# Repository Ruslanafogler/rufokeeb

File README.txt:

A personal keyboard I am developing from scratch using kicad for fun! Attached are the pcb files and gerbers invovled, BOM is also included. 67% keeb, based off of the KBD67 Lite.

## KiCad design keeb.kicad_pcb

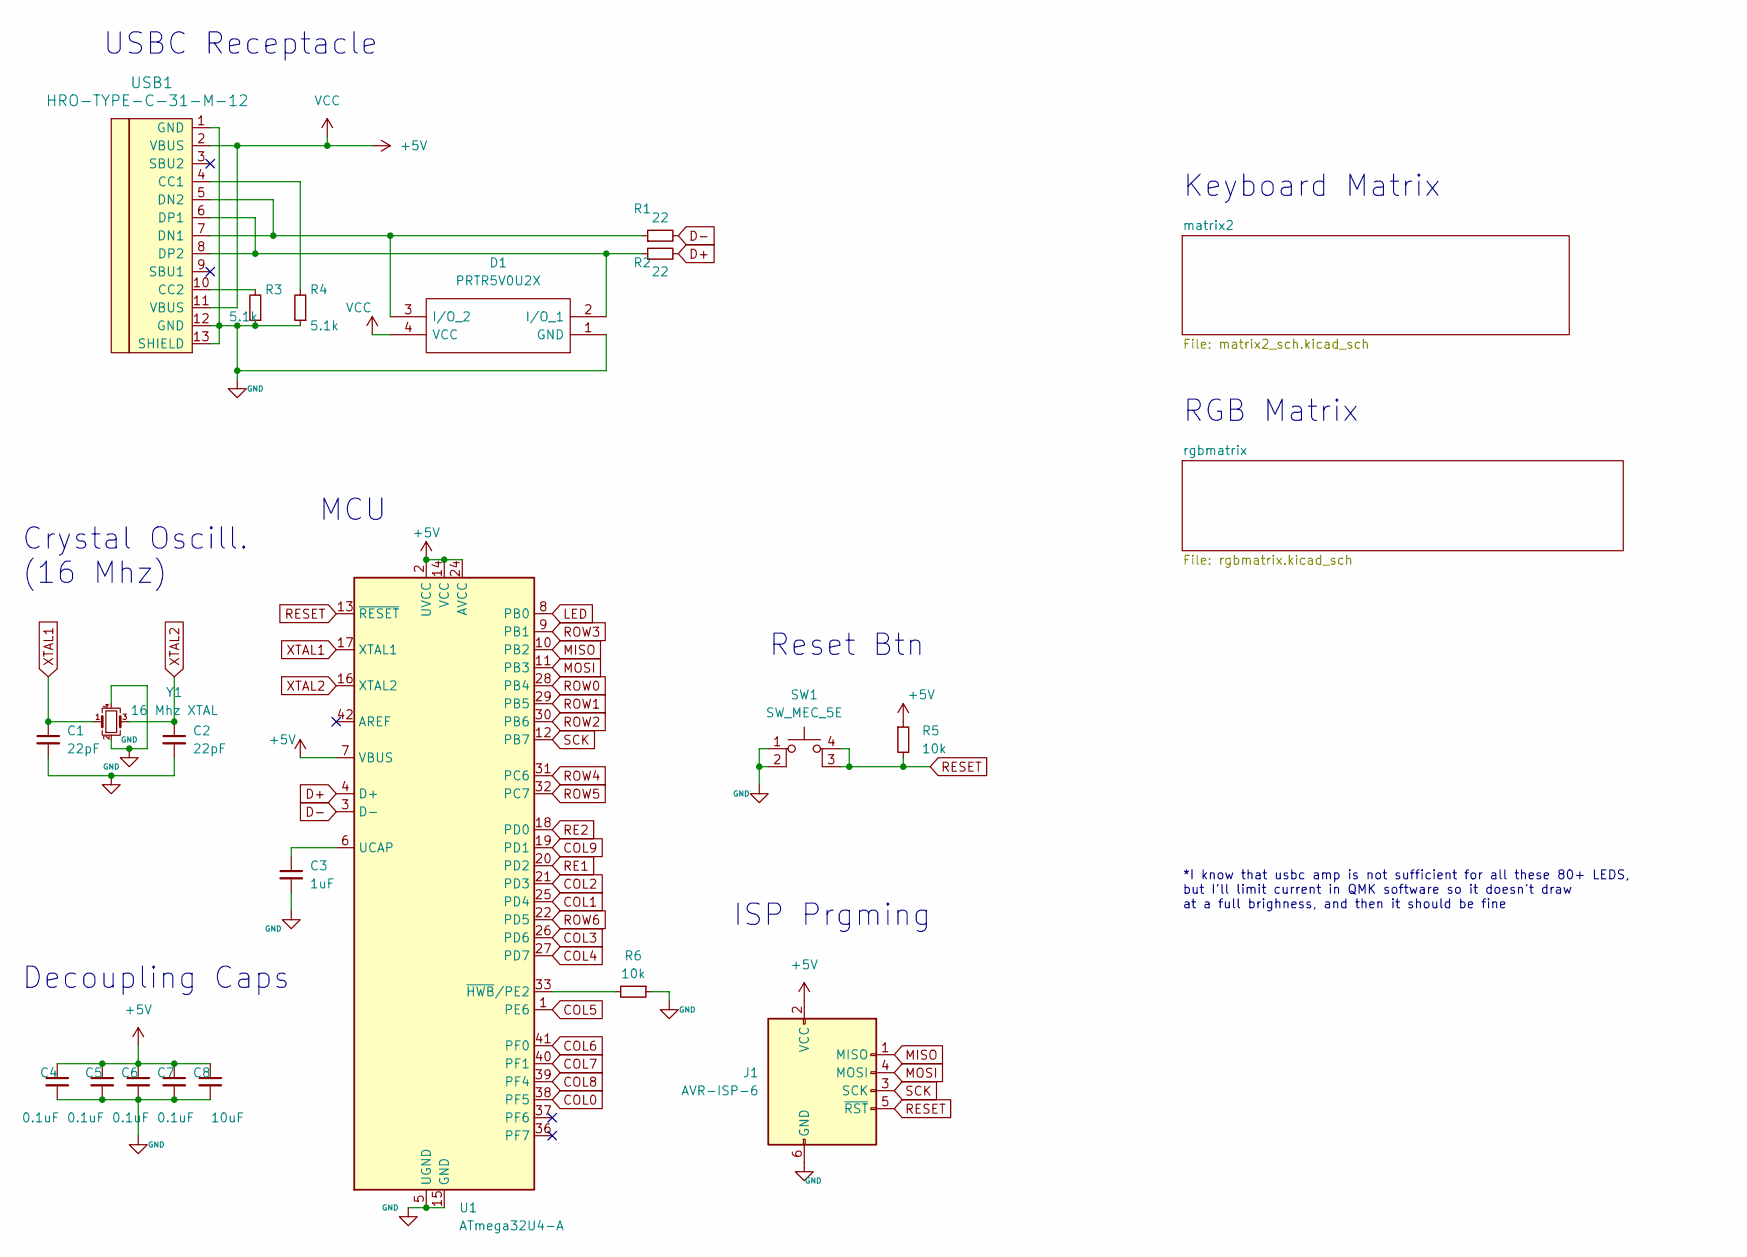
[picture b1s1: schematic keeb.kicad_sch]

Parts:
C1, C2: 22pF; C_0805_2012Metric_Pad1.18x1.45mm_HandSolder
C3: 1uF; C_0805_2012Metric_Pad1.18x1.45mm_HandSolder
C4, C5, C6, C7: 0.1uF; C_0805_2012Metric_Pad1.18x1.45mm_HandSolder
C8: 10uF; C_0805_2012Metric_Pad1.18x1.45mm_HandSolder
D1: PRTR5V0U2X; SOT143B; Manufacturer_Part_Number PRTR5V0U2X; Mouser Part Number N/A
J1: AVR-ISP-6; Reset_Pretty-Mask
R1, R2: 22; R_0805_2012Metric_Pad1.20x1.40mm_HandSolder
R3, R4: 5.1k; R_0805_2012Metric_Pad1.20x1.40mm_HandSolder
R5, R6: 10k; R_0805_2012Metric_Pad1.20x1.40mm_HandSolder
SW1: SW_MEC_5E; SW_MEC_5GSH9
U1: ATmega32U4-A; TQFP-44_10x10mm_P0.8mm
USB1: HRO-TYPE-C-31-M-12; HRO-TYPE-C-31-M-12-HandSoldering
Y1: 16 Mhz XTAL; Crystal_SMD_3225-4Pin_3.2x2.5mm_HandSoldering

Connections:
+5V: C4.1, C5.1, C6.1, C7.1, C8.1, D1.4 (VCC), J1.2 (VCC), R5.1, U1.2 (UVCC), U1.7 (VBUS), U1.14 (VCC), U1.24 (AVCC), U1.34 (VCC), U1.44 (AVCC), USB1.2 (VBUS), USB1.11 (VBUS); also elsewhere on the board
COL0: U1.38 (PF5); also elsewhere on the board
COL1: U1.25 (PD4); also elsewhere on the board
COL2: U1.21 (PD3); also elsewhere on the board
COL3: U1.26 (PD6); also elsewhere on the board
COL4: U1.27 (PD7); also elsewhere on the board
COL5: U1.1 (PE6); also elsewhere on the board
COL6: U1.41 (PF0); also elsewhere on the board
COL7: U1.40 (PF1); also elsewhere on the board
COL8: U1.39 (PF4); also elsewhere on the board
COL9: U1.19 (PD1); also elsewhere on the board
D+: R2.2, U1.4 (D+)
D-: R1.2, U1.3 (D-)
GND: C1.2, C2.2, C3.2, C4.2, C5.2, C6.2, C7.2, C8.2, D1.1 (GND), J1.6 (GND), R3.1, R4.1, R6.1, SW1.1, SW1.2, U1.5 (UGND), U1.15 (GND), U1.23 (GND), U1.35 (GND), U1.43 (GND), USB1.1 (GND), USB1.12 (GND), USB1.13 (SHIELD), Y1.2, Y1.4; also elsewhere on the board
LED: U1.8 (PB0); also elsewhere on the board
unnamed: C3.1, U1.6 (UCAP)
unnamed: D1.2 (I/O_1), R2.1, USB1.6 (DP1), USB1.8 (DP2)
unnamed: D1.3 (I/O_2), R1.1, USB1.5 (DN2), USB1.7 (DN1)
unnamed: R3.2, USB1.10 (CC2)
unnamed: R4.2, USB1.4 (CC1)
unnamed: R6.2, U1.33 (~HWB/PE2)
RE1: U1.20 (PD2); also elsewhere on the board
RE2: U1.18 (PD0); also elsewhere on the board
RESET: J1.5 (~RST), R5.2, SW1.3 (K), SW1.4 (A), U1.13 (~RESET); also elsewhere on the board
ROW0: U1.28 (PB4); also elsewhere on the board
ROW1: U1.29 (PB5); also elsewhere on the board
ROW2: U1.30 (PB6); also elsewhere on the board
ROW4: U1.31 (PC6); also elsewhere on the board
ROW5: U1.32 (PC7); also elsewhere on the board
ROW6: U1.22 (PD5); also elsewhere on the board
XTAL1: C1.1, U1.17 (XTAL1), Y1.1
XTAL2: C2.1, U1.16 (XTAL2), Y1.3

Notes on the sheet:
MCU
ISP Prgming
RGB Matrix
Reset Btn
USBC Receptacle
Keyboard Matrix
Crystal Oscill. (16 Mhz)
Decoupling Caps
*I know that usbc amp is not sufficient for all these 80+ LEDS, but I'll limit current in QMK software so it doesn't draw at a full brighness, and then it should be fine

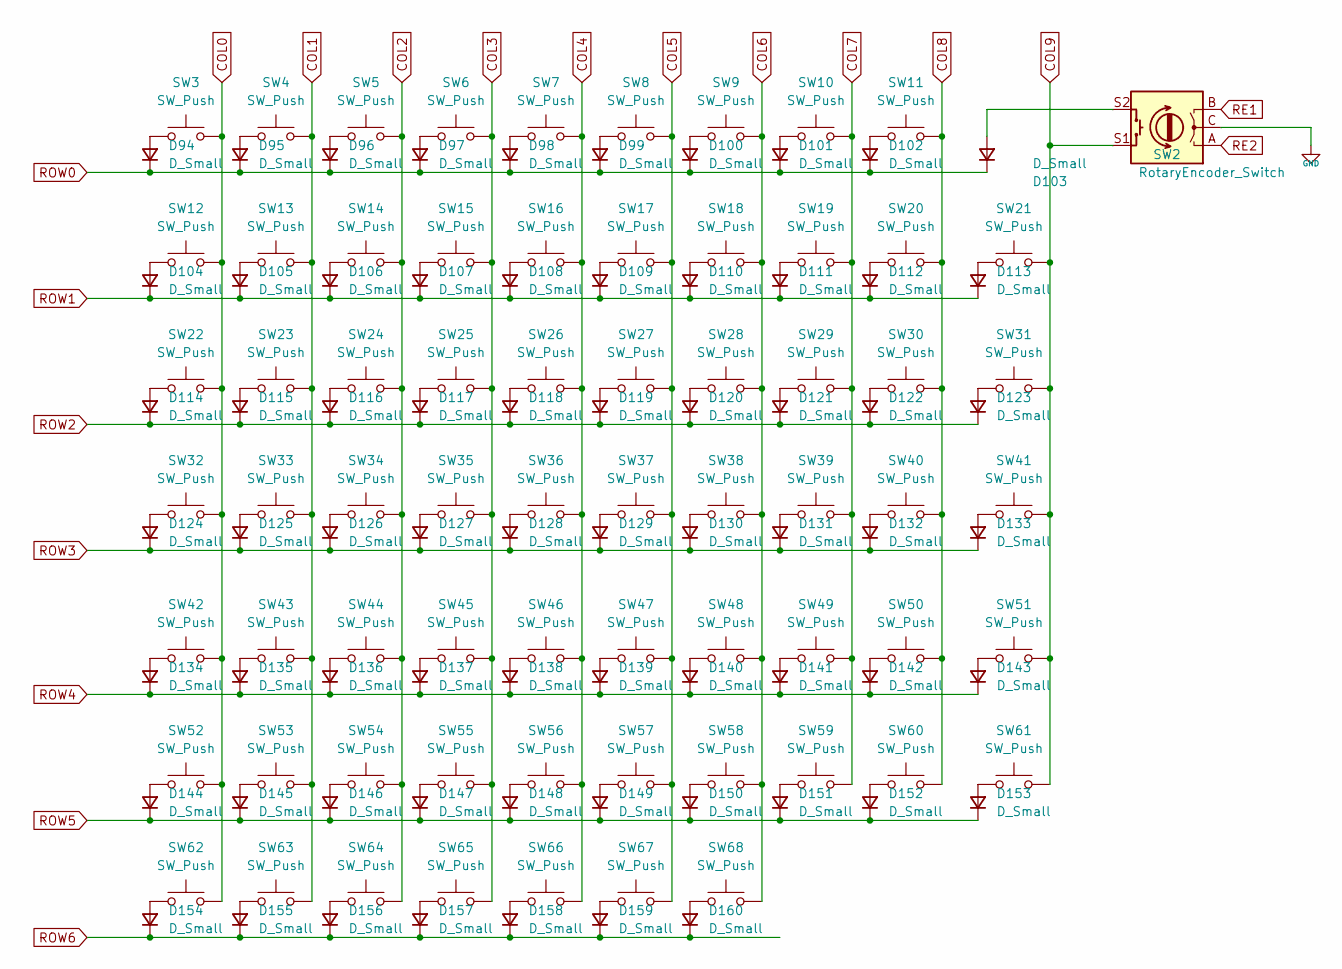
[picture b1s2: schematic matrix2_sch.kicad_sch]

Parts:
D94, D95, D96, D97, D98, D99, D100, D101, D102, D103, D104, D105, D106, D107, D108, D109, D110, D111, D112, D113, D114, D115, D116, D117, D118, D119, D120, D121, D122, D123, D124, D125, D126, D127, D128, D129, D130, D131, D132, D133, D134, D135, D136, D137, D138, D139, D140, D141, D142, D143, D144, D145, D146, D147, D148, D149, D150, D151, D152, D153, D154, D155, D156, D157, D158, D159, D160: D_Small; D_SOD-123
SW2: RotaryEncoder_Switch; RotaryEncoder_Alps_EC11E-Switch_Vertical_H20mm_CircularMoun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
SW3, SW4, SW5, SW6, SW7, SW8, SW9, SW10, SW11, SW12, SW13, SW14, SW15, SW18, SW19, SW20, SW21, SW22, SW23, SW24, SW25, SW26, SW27, SW28, SW29, SW31, SW33, SW34, SW35, SW36, SW37, SW38, SW39, SW40, SW41, SW42, SW43, SW45, SW47, SW48, SW49, SW50, SW51, SW52, SW53, SW54, SW55, SW56, SW58, SW59, SW66, SW67, SW68: SW_Push; MX100H
SW16: SW_Push; MX200HR
SW17, SW30: SW_Push; MX150H
SW32, SW57: SW_Push; MX175H
SW44, SW46: SW_Push; MX225HR
SW60, SW61, SW62, SW64, SW65: SW_Push; MX125H
SW63: SW_Push; MX625HR

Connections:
COL0: SW3.2, SW12.2, SW22.2, SW32.2, SW42.2, SW52.2, SW62.2; also elsewhere on the board
COL1: SW4.2, SW13.2, SW23.2, SW33.2, SW43.2, SW53.2, SW63.2; also elsewhere on the board
COL2: SW5.2, SW14.2, SW24.2, SW34.2, SW44.2, SW54.2, SW64.2; also elsewhere on the board
COL3: SW6.2, SW15.2, SW25.2, SW35.2, SW45.2, SW55.2, SW65.2; also elsewhere on the board
COL4: SW7.2, SW16.2, SW26.2, SW36.2, SW46.2, SW56.2, SW66.2; also elsewhere on the board
COL5: SW8.2, SW17.2, SW27.2, SW37.2, SW47.2, SW57.2, SW67.2; also elsewhere on the board
COL6: SW9.2, SW18.2, SW28.2, SW38.2, SW48.2, SW58.2, SW68.2; also elsewhere on the board
COL7: SW10.2, SW19.2, SW29.2, SW39.2, SW49.2, SW59.2; also elsewhere on the board
COL8: SW11.2, SW20.2, SW30.2, SW40.2, SW50.2, SW60.2; also elsewhere on the board
COL9: SW2.S1, SW21.2, SW31.2, SW41.2, SW51.2, SW61.2; also elsewhere on the board
GND: SW2.C; also elsewhere on the board
unnamed: D94.2 (A), SW3.1
unnamed: D95.2 (A), SW4.1
unnamed: D96.2 (A), SW5.1
unnamed: D97.2 (A), SW6.1
unnamed: D98.2 (A), SW7.1
unnamed: D99.2 (A), SW8.1
unnamed: D100.2 (A), SW9.1
unnamed: D101.2 (A), SW10.1
unnamed: D102.2 (A), SW11.1
unnamed: D103.2 (A), SW2.S2
unnamed: D104.2 (A), SW12.1
unnamed: D105.2 (A), SW13.1
unnamed: D106.2 (A), SW14.1
unnamed: D107.2 (A), SW15.1
unnamed: D108.2 (A), SW16.1
unnamed: D109.2 (A), SW17.1
unnamed: D110.2 (A), SW18.1
unnamed: D111.2 (A), SW19.1
unnamed: D112.2 (A), SW20.1
unnamed: D113.2 (A), SW21.1
unnamed: D114.2 (A), SW22.1
unnamed: D115.2 (A), SW23.1
unnamed: D116.2 (A), SW24.1
unnamed: D117.2 (A), SW25.1
unnamed: D118.2 (A), SW26.1
unnamed: D119.2 (A), SW27.1
unnamed: D120.2 (A), SW28.1
unnamed: D121.2 (A), SW29.1
unnamed: D122.2 (A), SW30.1
unnamed: D123.2 (A), SW31.1
unnamed: D124.2 (A), SW32.1
unnamed: D125.2 (A), SW33.1
unnamed: D126.2 (A), SW34.1
unnamed: D127.2 (A), SW35.1
unnamed: D128.2 (A), SW36.1
unnamed: D129.2 (A), SW37.1
unnamed: D130.2 (A), SW38.1
unnamed: D131.2 (A), SW39.1
unnamed: D132.2 (A), SW40.1
unnamed: D133.2 (A), SW41.1
unnamed: D134.2 (A), SW42.1
unnamed: D135.2 (A), SW43.1
unnamed: D136.2 (A), SW44.1
unnamed: D137.2 (A), SW45.1
unnamed: D138.2 (A), SW46.1
unnamed: D139.2 (A), SW47.1
unnamed: D140.2 (A), SW48.1
unnamed: D141.2 (A), SW49.1
unnamed: D142.2 (A), SW50.1
unnamed: D143.2 (A), SW51.1
unnamed: D144.2 (A), SW52.1
unnamed: D145.2 (A), SW53.1
unnamed: D146.2 (A), SW54.1
unnamed: D147.2 (A), SW55.1
unnamed: D148.2 (A), SW56.1
unnamed: D149.2 (A), SW57.1
unnamed: D150.2 (A), SW58.1
unnamed: D151.2 (A), SW59.1
unnamed: D152.2 (A), SW60.1
unnamed: D153.2 (A), SW61.1
unnamed: D154.2 (A), SW62.1
unnamed: D155.2 (A), SW63.1
unnamed: D156.2 (A), SW64.1
unnamed: D157.2 (A), SW65.1
unnamed: D158.2 (A), SW66.1
unnamed: D159.2 (A), SW67.1
unnamed: D160.2 (A), SW68.1
RE1: SW2.B; also elsewhere on the board
RE2: SW2.A; also elsewhere on the board
ROW0: D94.1 (K), D95.1 (K), D96.1 (K), D97.1 (K), D98.1 (K), D99.1 (K), D100.1 (K), D101.1 (K), D102.1 (K), D103.1 (K); also elsewhere on the board
ROW1: D104.1 (K), D105.1 (K), D106.1 (K), D107.1 (K), D108.1 (K), D109.1 (K), D110.1 (K), D111.1 (K), D112.1 (K), D113.1 (K); also elsewhere on the board
ROW2: D114.1 (K), D115.1 (K), D116.1 (K), D117.1 (K), D118.1 (K), D119.1 (K), D120.1 (K), D121.1 (K), D122.1 (K), D123.1 (K); also elsewhere on the board
ROW4: D134.1 (K), D135.1 (K), D136.1 (K), D137.1 (K), D138.1 (K), D139.1 (K), D140.1 (K), D141.1 (K), D142.1 (K), D143.1 (K); also elsewhere on the board
ROW5: D144.1 (K), D145.1 (K), D146.1 (K), D147.1 (K), D148.1 (K), D149.1 (K), D150.1 (K), D151.1 (K), D152.1 (K), D153.1 (K); also elsewhere on the board
ROW6: D154.1 (K), D155.1 (K), D156.1 (K), D157.1 (K), D158.1 (K), D159.1 (K), D160.1 (K); also elsewhere on the board

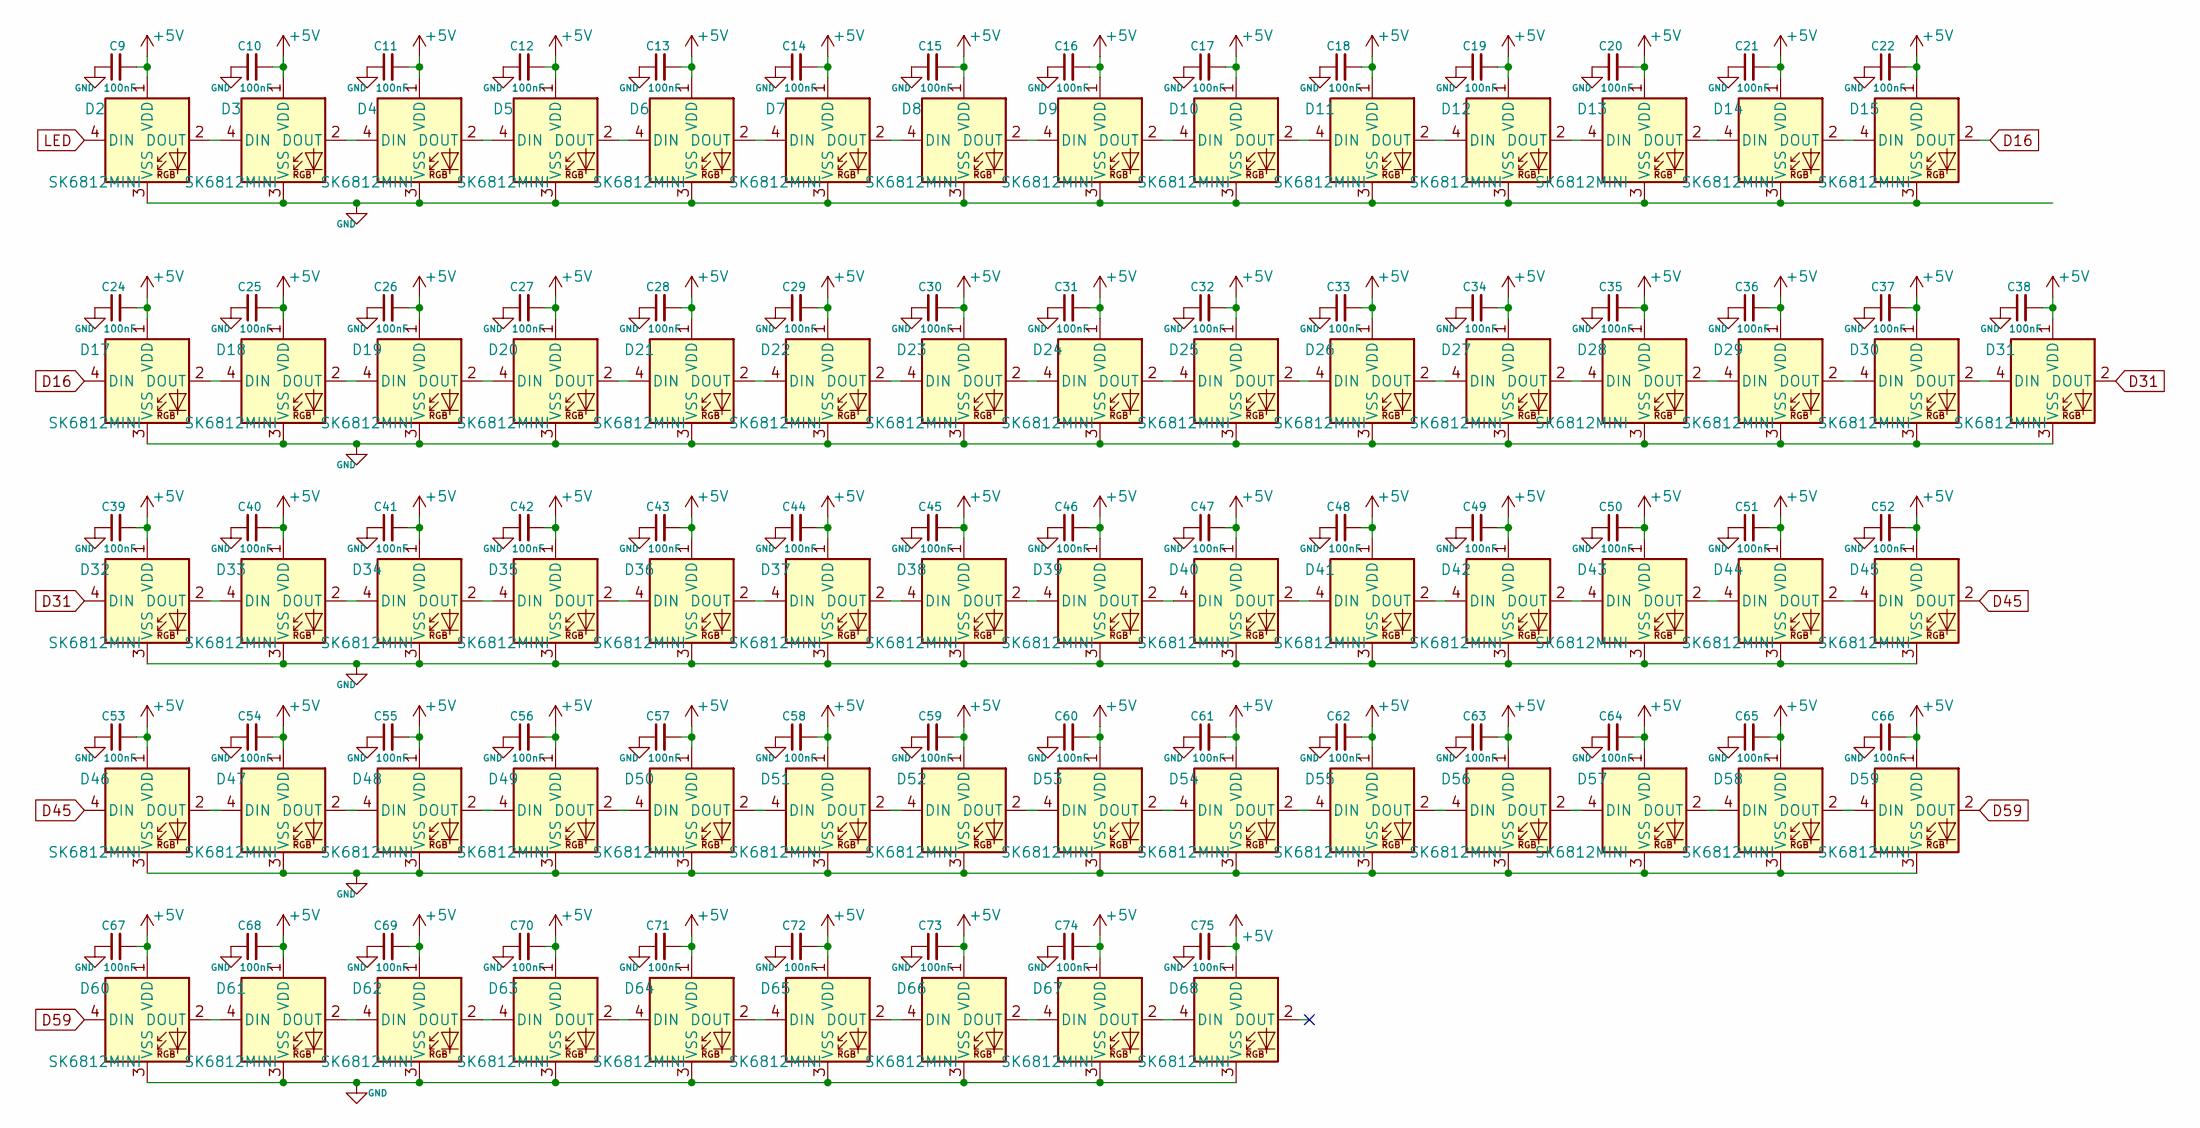
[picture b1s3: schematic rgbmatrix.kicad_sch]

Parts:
C9, C10, C11, C12, C13, C14, C15, C16, C17, C18, C19, C20, C21, C22, C24, C25, C26, C27, C28, C29, C30, C31, C32, C33, C34, C35, C36, C37, C38, C39, C40, C41, C42, C43, C44, C45, C46, C47, C48, C49, C50, C51, C52, C53, C54, C55, C56, C57, C58, C59, C60, C61, C62, C63, C64, C65, C66, C67, C68, C69, C70, C71, C72, C73, C74, C75: 100nF; C_0805_2012Metric_Pad1.18x1.45mm_HandSolder
D2, D3, D4, D5, D6, D7, D8, D9, D10, D11, D12, D13, D14, D15, D17, D18, D19, D20, D21, D22, D23, D24, D25, D26, D27, D28, D29, D30, D31, D32, D33, D34, D35, D36, D37, D38, D39, D40, D41, D42, D43, D44, D45, D46, D47, D48, D49, D50, D51, D52, D53, D54, D55, D56, D57, D58, D59, D60, D61, D62, D63, D64, D65, D66, D67, D68: SK6812MINI; MX_SK6812MINI-E_REV

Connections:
+5V: C9.2, C10.2, C11.2, C12.2, C13.2, C14.2, C15.2, C16.2, C17.2, C18.2, C19.2, C20.2, C21.2, C22.2, C24.2, C25.2, C26.2, C27.2, C28.2, C29.2, C30.2, C31.2, C32.2, C33.2, C34.2, C35.2, C36.2, C37.2, C38.2, C39.2, C40.2, C41.2, C42.2, C43.2, C44.2, C45.2, C46.2, C47.2, C48.2, C49.2, C50.2, C51.2, C52.2, C53.2, C54.2, C55.2, C56.2, C57.2, C58.2, C59.2, C60.2, C61.2, C62.2, C63.2, C64.2, C65.2, C66.2, C67.2, C68.2, C69.2, C70.2, C71.2, C72.2, C73.2, C74.2, C75.2, D2.1 (VDD), D3.1 (VDD), D4.1 (VDD), D5.1 (VDD), D6.1 (VDD), D7.1 (VDD), D8.1 (VDD), D9.1 (VDD), D10.1 (VDD), D11.1 (VDD), D12.1 (VDD), D13.1 (VDD), D14.1 (VDD), D15.1 (VDD), D17.1 (VDD), D18.1 (VDD), D19.1 (VDD), D20.1 (VDD), D21.1 (VDD), D22.1 (VDD), D23.1 (VDD), D24.1 (VDD), D25.1 (VDD), D26.1 (VDD), D27.1 (VDD), D28.1 (VDD), D29.1 (VDD), D30.1 (VDD), D31.1 (VDD), D32.1 (VDD), D33.1 (VDD), D34.1 (VDD), D35.1 (VDD), D36.1 (VDD), D37.1 (VDD), D38.1 (VDD), D39.1 (VDD), D40.1 (VDD), D41.1 (VDD), D42.1 (VDD), D43.1 (VDD), D44.1 (VDD), D45.1 (VDD), D46.1 (VDD), D47.1 (VDD), D48.1 (VDD), D49.1 (VDD), D50.1 (VDD), D51.1 (VDD), D52.1 (VDD), D53.1 (VDD), D54.1 (VDD), D55.1 (VDD), D56.1 (VDD), D57.1 (VDD), D58.1 (VDD), D59.1 (VDD), D60.1 (VDD), D61.1 (VDD), D62.1 (VDD), D63.1 (VDD), D64.1 (VDD), D65.1 (VDD), D66.1 (VDD), D67.1 (VDD), D68.1 (VDD); also elsewhere on the board
D16: D15.2 (DOUT), D17.4 (DIN)
D31: D31.2 (DOUT), D32.4 (DIN)
D45: D45.2 (DOUT), D46.4 (DIN)
D59: D59.2 (DOUT), D60.4 (DIN)
GND: C9.1, C10.1, C11.1, C12.1, C13.1, C14.1, C15.1, C16.1, C17.1, C18.1, C19.1, C20.1, C21.1, C22.1, C24.1, C25.1, C26.1, C27.1, C28.1, C29.1, C30.1, C31.1, C32.1, C33.1, C34.1, C35.1, C36.1, C37.1, C38.1, C39.1, C40.1, C41.1, C42.1, C43.1, C44.1, C45.1, C46.1, C47.1, C48.1, C49.1, C50.1, C51.1, C52.1, C53.1, C54.1, C55.1, C56.1, C57.1, C58.1, C59.1, C60.1, C61.1, C62.1, C63.1, C64.1, C65.1, C66.1, C67.1, C68.1, C69.1, C70.1, C71.1, C72.1, C73.1, C74.1, C75.1, D2.3 (VSS), D3.3 (VSS), D4.3 (VSS), D5.3 (VSS), D6.3 (VSS), D7.3 (VSS), D8.3 (VSS), D9.3 (VSS), D10.3 (VSS), D11.3 (VSS), D12.3 (VSS), D13.3 (VSS), D14.3 (VSS), D15.3 (VSS), D17.3 (VSS), D18.3 (VSS), D19.3 (VSS), D20.3 (VSS), D21.3 (VSS), D22.3 (VSS), D23.3 (VSS), D24.3 (VSS), D25.3 (VSS), D26.3 (VSS), D27.3 (VSS), D28.3 (VSS), D29.3 (VSS), D30.3 (VSS), D31.3 (VSS), D32.3 (VSS), D33.3 (VSS), D34.3 (VSS), D35.3 (VSS), D36.3 (VSS), D37.3 (VSS), D38.3 (VSS), D39.3 (VSS), D40.3 (VSS), D41.3 (VSS), D42.3 (VSS), D43.3 (VSS), D44.3 (VSS), D45.3 (VSS), D46.3 (VSS), D47.3 (VSS), D48.3 (VSS), D49.3 (VSS), D50.3 (VSS), D51.3 (VSS), D52.3 (VSS), D53.3 (VSS), D54.3 (VSS), D55.3 (VSS), D56.3 (VSS), D57.3 (VSS), D58.3 (VSS), D59.3 (VSS), D60.3 (VSS), D61.3 (VSS), D62.3 (VSS), D63.3 (VSS), D64.3 (VSS), D65.3 (VSS), D66.3 (VSS), D67.3 (VSS), D68.3 (VSS); also elsewhere on the board
LED: D2.4 (DIN); also elsewhere on the board
unnamed: D2.2 (DOUT), D3.4 (DIN)
unnamed: D3.2 (DOUT), D4.4 (DIN)
unnamed: D4.2 (DOUT), D5.4 (DIN)
unnamed: D5.2 (DOUT), D6.4 (DIN)
unnamed: D6.2 (DOUT), D7.4 (DIN)
unnamed: D7.2 (DOUT), D8.4 (DIN)
unnamed: D8.2 (DOUT), D9.4 (DIN)
unnamed: D10.2 (DOUT), D11.4 (DIN)
unnamed: D9.2 (DOUT), D10.4 (DIN)
unnamed: D11.2 (DOUT), D12.4 (DIN)
unnamed: D12.2 (DOUT), D13.4 (DIN)
unnamed: D13.2 (DOUT), D14.4 (DIN)
unnamed: D14.2 (DOUT), D15.4 (DIN)
unnamed: D17.2 (DOUT), D18.4 (DIN)
unnamed: D18.2 (DOUT), D19.4 (DIN)
unnamed: D19.2 (DOUT), D20.4 (DIN)
unnamed: D20.2 (DOUT), D21.4 (DIN)
unnamed: D21.2 (DOUT), D22.4 (DIN)
unnamed: D22.2 (DOUT), D23.4 (DIN)
unnamed: D23.2 (DOUT), D24.4 (DIN)
unnamed: D24.2 (DOUT), D25.4 (DIN)
unnamed: D25.2 (DOUT), D26.4 (DIN)
unnamed: D26.2 (DOUT), D27.4 (DIN)
unnamed: D27.2 (DOUT), D28.4 (DIN)
unnamed: D28.2 (DOUT), D29.4 (DIN)
unnamed: D29.2 (DOUT), D30.4 (DIN)
unnamed: D30.2 (DOUT), D31.4 (DIN)
unnamed: D32.2 (DOUT), D33.4 (DIN)
unnamed: D33.2 (DOUT), D34.4 (DIN)
unnamed: D34.2 (DOUT), D35.4 (DIN)
unnamed: D35.2 (DOUT), D36.4 (DIN)
unnamed: D36.2 (DOUT), D37.4 (DIN)
unnamed: D37.2 (DOUT), D38.4 (DIN)
unnamed: D38.2 (DOUT), D39.4 (DIN)
unnamed: D39.2 (DOUT), D40.4 (DIN)
unnamed: D40.2 (DOUT), D41.4 (DIN)
unnamed: D41.2 (DOUT), D42.4 (DIN)
unnamed: D42.2 (DOUT), D43.4 (DIN)
unnamed: D43.2 (DOUT), D44.4 (DIN)
unnamed: D44.2 (DOUT), D45.4 (DIN)
unnamed: D46.2 (DOUT), D47.4 (DIN)
unnamed: D47.2 (DOUT), D48.4 (DIN)
unnamed: D48.2 (DOUT), D49.4 (DIN)
unnamed: D49.2 (DOUT), D50.4 (DIN)
unnamed: D50.2 (DOUT), D51.4 (DIN)
unnamed: D51.2 (DOUT), D52.4 (DIN)
unnamed: D52.2 (DOUT), D53.4 (DIN)
unnamed: D53.2 (DOUT), D54.4 (DIN)
unnamed: D54.2 (DOUT), D55.4 (DIN)
unnamed: D55.2 (DOUT), D56.4 (DIN)
unnamed: D56.2 (DOUT), D57.4 (DIN)
unnamed: D57.2 (DOUT), D58.4 (DIN)
unnamed: D58.2 (DOUT), D59.4 (DIN)
unnamed: D60.2 (DOUT), D61.4 (DIN)
unnamed: D61.2 (DOUT), D62.4 (DIN)
unnamed: D62.2 (DOUT), D63.4 (DIN)
unnamed: D63.2 (DOUT), D64.4 (DIN)
unnamed: D64.2 (DOUT), D65.4 (DIN)
unnamed: D65.2 (DOUT), D66.4 (DIN)
unnamed: D66.2 (DOUT), D67.4 (DIN)
unnamed: D67.2 (DOUT), D68.4 (DIN)

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
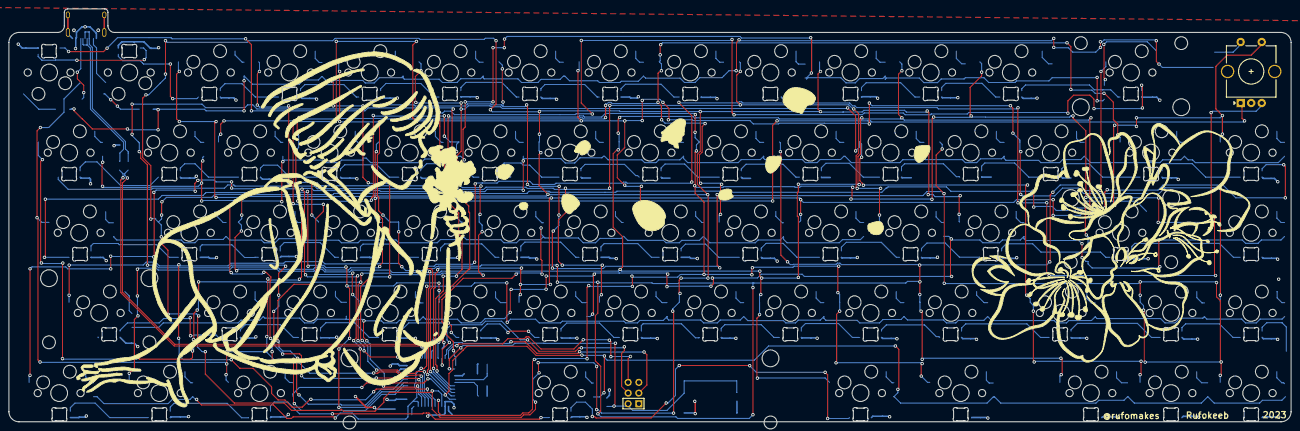
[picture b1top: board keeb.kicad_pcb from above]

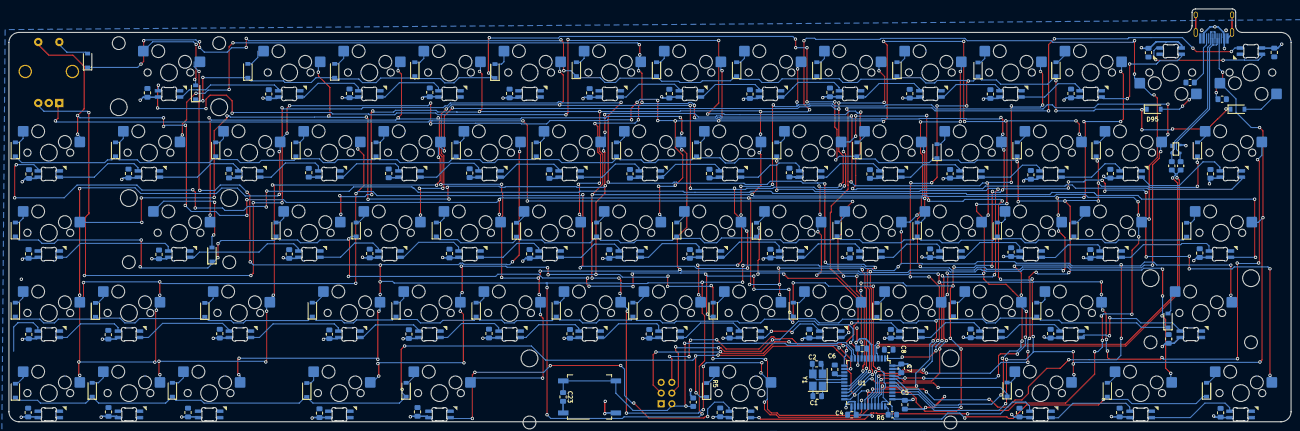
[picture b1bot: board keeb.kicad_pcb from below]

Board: 2 copper layers, 304.8 x 98.1 mm, 287 parts (219 on the bottom side), 168 nets.

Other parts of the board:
C23: 100nF; C_0805_2012Metric_Pad1.18x1.45mm_HandSolder
C23#2: 0.1uF; C_0805_2012Metric_Pad1.18x1.45mm_HandSolder

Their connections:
+5V: C23.2; also elsewhere on the board
GND: C23.1, C23#2.2; also elsewhere on the board
RESET: C23#2.1; also elsewhere on the board

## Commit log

2022-12-27 first
2022-12-27 added submodds
2022-12-27 changed to 60 :C
2022-12-28 moved keys/neopixels
2022-12-28 strange short?
2022-12-28 placed caps first attempt
2022-12-31 began routing for real
2023-01-02 finished v1
2023-01-02 got rid of some tiny silkscreen overlaps
2023-01-08 restarted LOLL
2023-01-08 progress with redoing
2023-01-09 finished redo??!!?
2023-01-12 finished reouting, saving before redo
2023-01-13 better data/crystal and 5v/gnd routing, other fixes to make things compatible
2023-01-14 fixed case to fit kbd67 lite (with their website svg and some resizing)
2023-01-21 fixed edges
2023-01-28 fked up LEDs :C
2023-01-28 replaced LED's in appropriate places
2023-03-06 pensive
    changed LEDs aaaAAAAAAA
2023-03-10 swapped for neopixel LED complete-ish?
2023-03-12 removed cap labels
2023-03-25 changed LEDs fr, added deb to switch
2023-04-08 4/8 changes
    fixed clearance errors(and tried to make sure the only errs were silkscreen related), fixed programming pins, added a small cap to the reset button, fixed LEDs to match schematic AND footprints
2023-04-08 changed switch, fixed extra capacitor
2023-04-08 createred gerbers
2023-04-09 added amogus
2023-04-13 added BOM
